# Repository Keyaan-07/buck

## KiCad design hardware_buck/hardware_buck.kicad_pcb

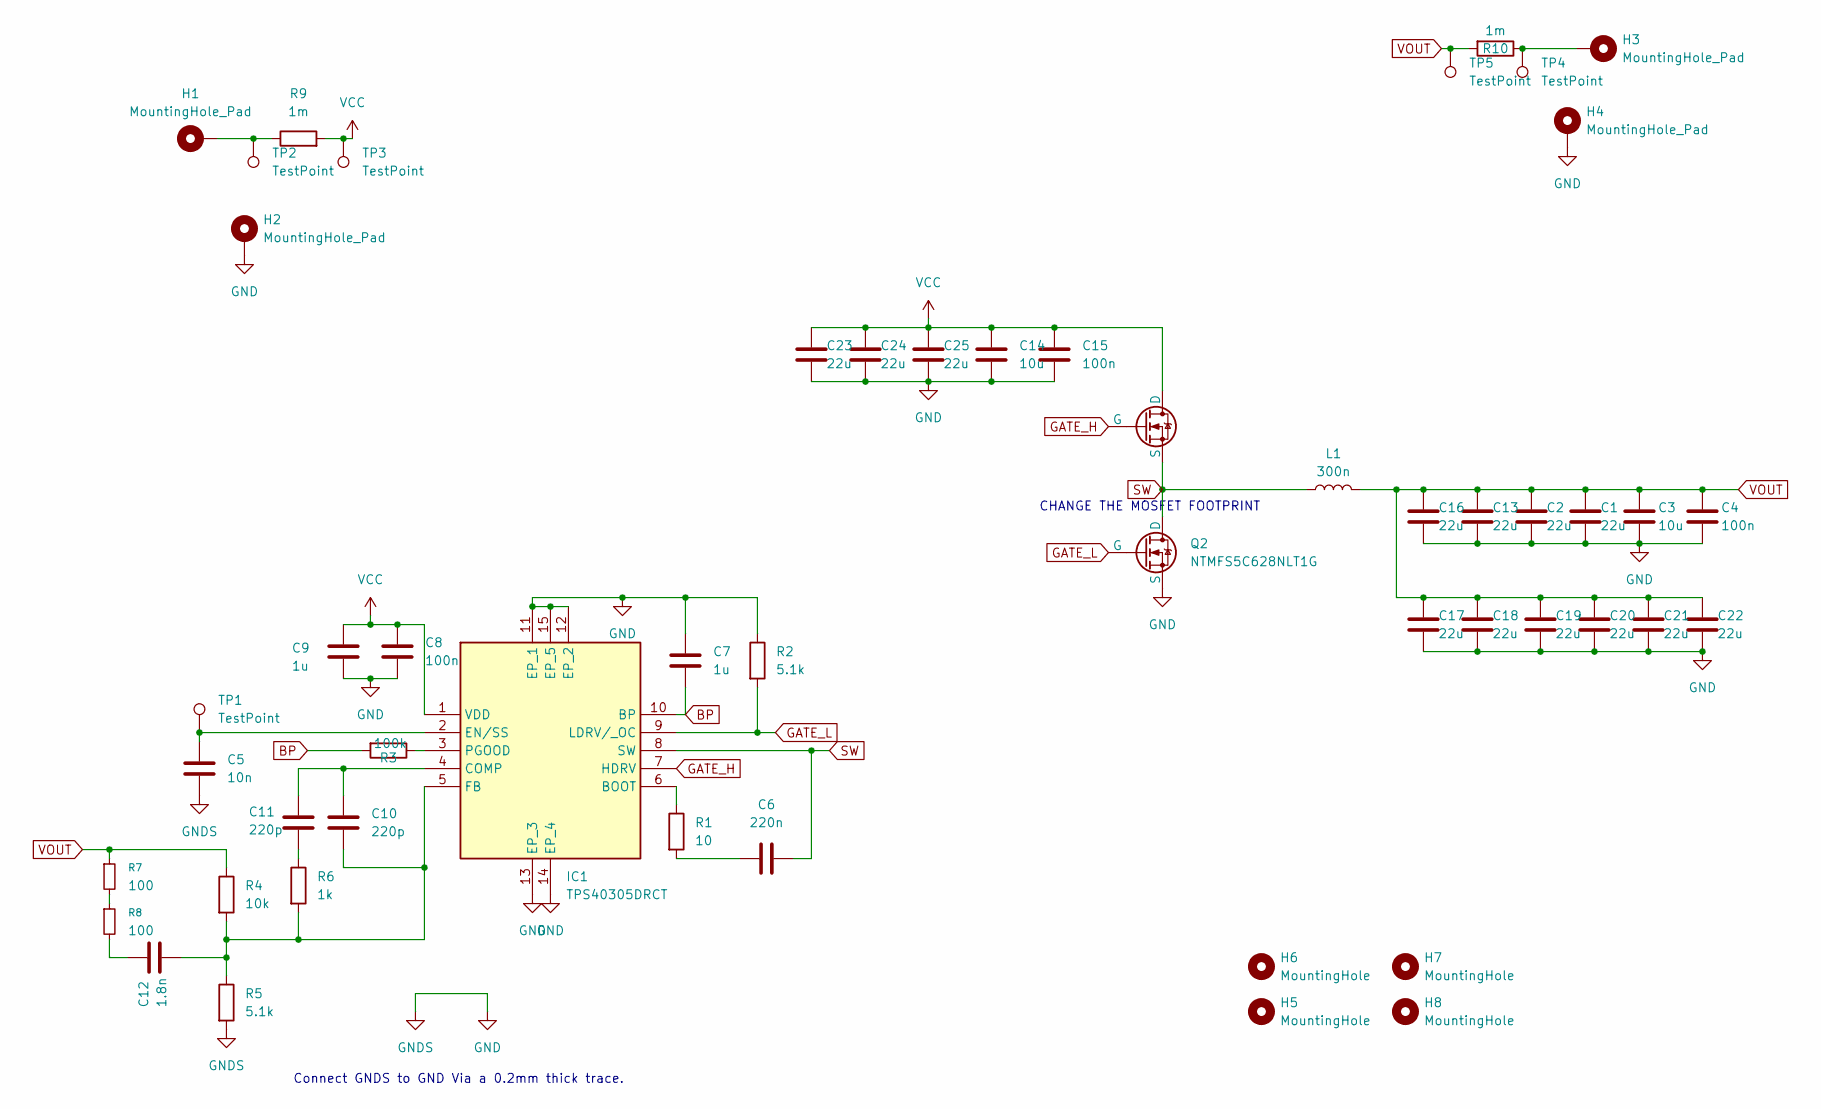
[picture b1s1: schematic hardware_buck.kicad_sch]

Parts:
C1, C2, C13, C16, C17, C18, C19, C20, C21, C22, C23, C24, C25: 22u; C_0805_2012Metric
C3, C14: 10u; C_0603_1608Metric
C4, C8, C15: 100n; C_0402_1005Metric
C5: 10n; C_0402_1005Metric
C6: 220n; C_0402_1005Metric
C7, C9: 1u; C_0402_1005Metric
C10, C11: 220p; C_0402_1005Metric
C12: 1.8n; C_0402_1005Metric
H1, H2, H3, H4: MountingHole_Pad; MountingHole_2.5mm_Pad_Via
H5, H6, H7, H8: MountingHole; MountingHole_2.1mm
IC1: TPS40305DRCT; Mouser Part Number 595-TPS40305DRCT
L1: 300n; L_7.3x7.3_H4.5
Q1, Q2: NTMFS5C628NLT1G; NTMFS5C460NLT1G
R1: 10; R_0402_1005Metric
R2, R5: 5.1k; R_0402_1005Metric
R3: 100k; R_0402_1005Metric
R4: 10k; R_0402_1005Metric
R6: 1k; R_0402_1005Metric
R7, R8: 100; R_0402_1005Metric
R9, R10: 1m; R_1206_3216Metric
TP1: TestPoint; TestPoint_Pad_D1.0mm
TP2, TP3, TP4, TP5: TestPoint; TestPoint_Pad_D2.0mm

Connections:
BP: C7.1, IC1.10 (BP), R3.2
GATE_H: IC1.7 (HDRV), Q1.4 (G)
GATE_L: IC1.9 (LDRV/_OC), Q2.4 (G), R2.2
GND: C1.2, C2.2, C3.2, C4.2, C5.2, C7.2, C8.2, C9.2, C13.2, C14.2, C15.2, C16.2, C17.2, C18.2, C19.2, C20.2, C21.2, C22.2, C23.2, C24.2, C25.2, H2.1, H4.1, IC1.11 (EP_1), IC1.12 (EP_2), IC1.13 (EP_3), IC1.14 (EP_4), IC1.15 (EP_5), Q2.1 (S), Q2.2 (S), Q2.3 (S), R2.1, R5.2
unnamed: C6.1, R1.2
unnamed: C11.2, R6.1
unnamed: C12.1, R8.2
unnamed: H1.1, R9.1, TP2.1
unnamed: H3.1, R10.1, TP4.1
unnamed: IC1.6 (BOOT), R1.1
unnamed: C10.1, C11.1, IC1.4 (COMP)
unnamed: C5.1, IC1.2 (EN/SS), TP1.1
unnamed: C10.2, C12.2, IC1.5 (FB), R4.2, R5.1, R6.2
unnamed: IC1.3 (PGOOD), R3.1
unnamed: R7.2, R8.1
SW: C6.2, IC1.8 (SW), L1.1, Q1.1 (S), Q1.2 (S), Q1.3 (S), Q2.5 (D), Q2.6 (D), Q2.7 (D), Q2.8 (D), Q2.9 (D)
VCC: C8.1, C9.1, C14.1, C15.1, C23.1, C24.1, C25.1, IC1.1 (VDD), Q1.5 (D), Q1.6 (D), Q1.7 (D), Q1.8 (D), Q1.9 (D), R9.2, TP3.1
VOUT: C1.1, C2.1, C3.1, C4.1, C13.1, C16.1, C17.1, C18.1, C19.1, C20.1, C21.1, C22.1, L1.2, R4.1, R7.1, R10.2, TP5.1

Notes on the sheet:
Connect GNDS to GND Via a 0.2mm thick trace.
CHANGE THE MOSFET FOOTPRINT

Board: 2 copper layers, 52 parts (4 on the bottom side), 18 nets, no tracks yet.

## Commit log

2026-02-01 Power stage done
2026-02-01 schematic complete
2026-02-03 started with the PCB layout
